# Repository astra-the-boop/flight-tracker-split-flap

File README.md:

# Split flap flight-tracker display
---
## Images

## Whots this UwU?
It's a split flap display with 18 characters designed to show just enough info to track flights. It uses an ESP32 to send API requests to [AviationStack](https://docs.apilayer.com/aviationstack/docs/api-documentation) (oof, only 100 req/mo), and displays the info accordingly.

The display has 3 rows, the first row has 7 characters (1 showing logos, 2 showing airline IATA code, 4 showing flight number), the 2nd row has 6 characters showing the origin and destination airport, the 3rd row has 5 alphanumeric characters and shows flight status (INFLT, DELAY, CNCLD, BRDNG), or time (23:59, 5 DAYS, 5 HRS, 3H49M, etc) which could be configured to different modes (only show status, only show time, or switch between the two).

Each character is its own module and can function independently with 45 character positions each, and the PCB designs makes this simple to do. Each module also includes a magnet and a hall effect sensor for calibration.

## Dimensions
Each module by itself is 9cm wide, up to 14.5cm tall, and up to 10cm thick.
The entire system is 64.3cm wide, 47cm tall, and 15cm thick.

## CAD & PCB
This was designed in Onshape and KiCad.

## Other details:
This uses 1 ESP32 DevKit v1, 2 Arduino Unos, and 1 Arduino Mega. This is not the best way to do it, I only did this because I'm dead broke and that's what i had.
This project uses the MIT License.

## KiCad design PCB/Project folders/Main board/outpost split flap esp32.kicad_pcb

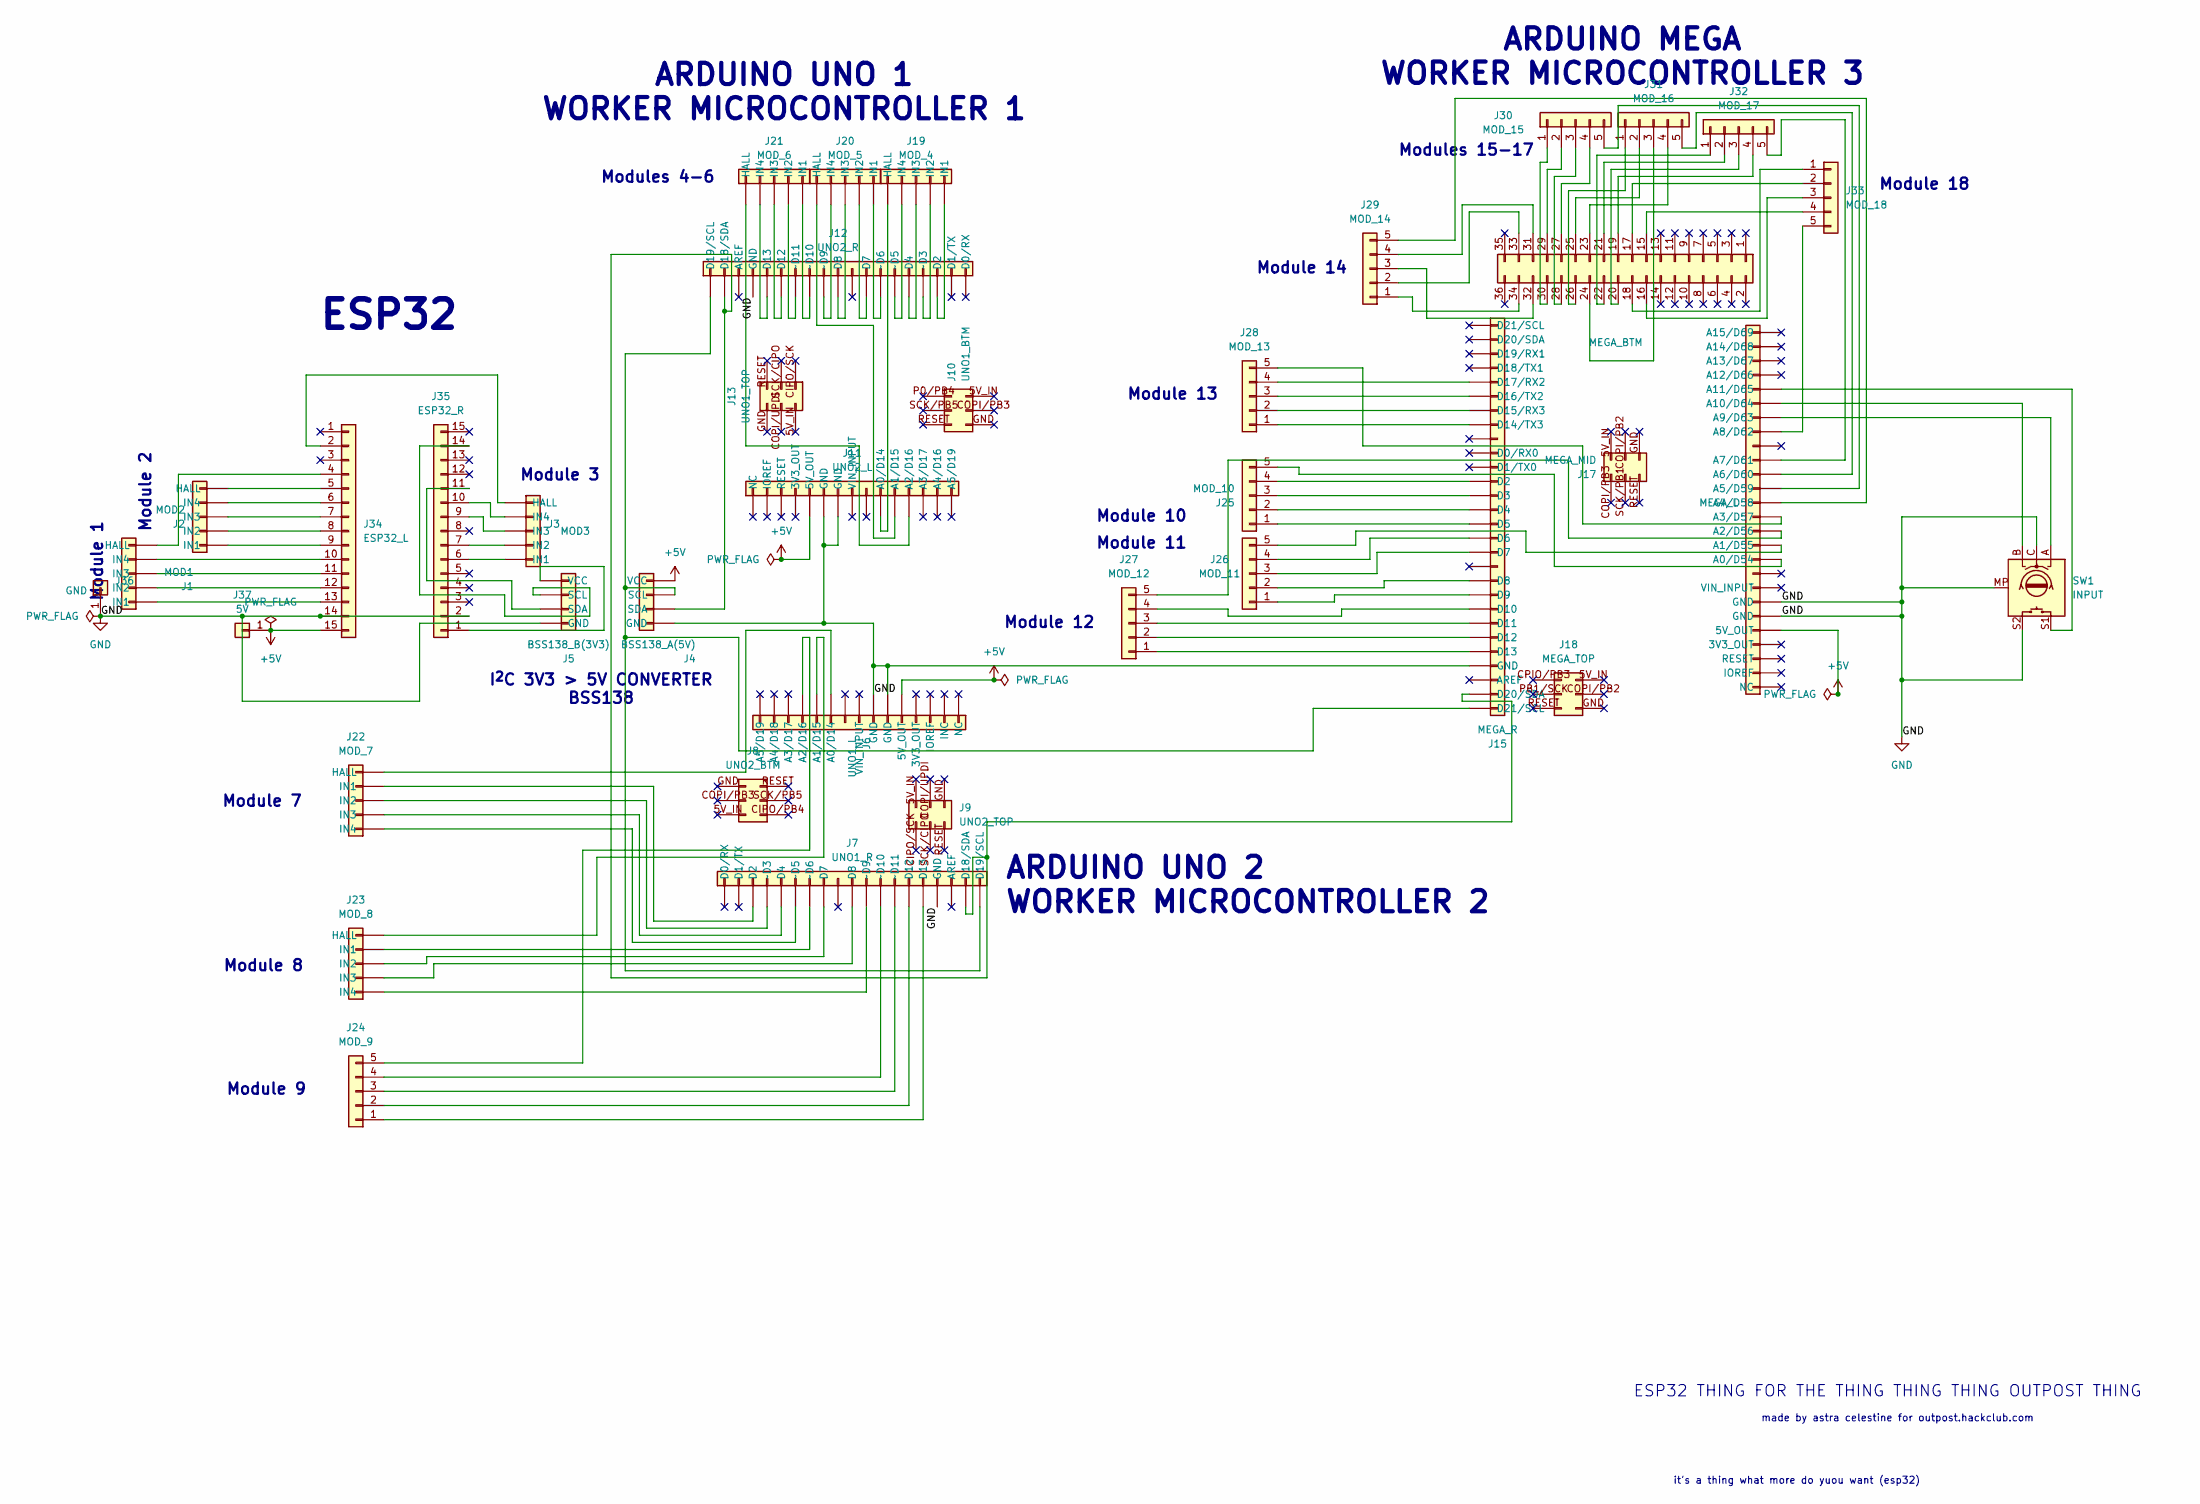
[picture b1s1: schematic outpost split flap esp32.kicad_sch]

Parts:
J1: MOD1; PinHeader_1x05_P2.54mm_Vertical
J2: MOD2; PinHeader_1x05_P2.54mm_Vertical
J3: MOD3; PinHeader_1x05_P2.54mm_Vertical
J4: BSS138_A(5V); PinHeader_1x04_P2.54mm_Vertical
J5: BSS138_B(3V3); PinHeader_1x04_P2.54mm_Vertical
J6: UNO1_L; PinHeader_1x15_P2.54mm_Vertical
J7: UNO1_R; PinHeader_1x19_P2.54mm_Vertical
J8: UNO2_BTM; PinHeader_2x03_P2.54mm_Vertical
J9: UNO2_TOP; PinHeader_2x03_P2.54mm_Vertical
J10: UNO1_BTM; PinHeader_2x03_P2.54mm_Vertical
J11: UNO2_L; PinHeader_1x15_P2.54mm_Vertical
J12: UNO2_R; PinHeader_1x19_P2.54mm_Vertical
J13: UNO1_TOP; PinHeader_2x03_P2.54mm_Vertical
J14: MEGA_L; PinHeader_1x26_P2.54mm_Vertical
J15: MEGA_R; PinHeader_1x28_P2.54mm_Vertical
J16: MEGA_BTM; PinHeader_2x18_P2.54mm_Vertical
J17: MEGA_MID; PinHeader_2x03_P2.54mm_Vertical
J18: MEGA_TOP; PinHeader_2x03_P2.54mm_Vertical
J19: MOD_4; PinHeader_1x05_P2.54mm_Vertical
J20: MOD_5; PinHeader_1x05_P2.54mm_Vertical
J21: MOD_6; PinHeader_1x05_P2.54mm_Vertical
J22: MOD_7; PinHeader_1x05_P2.54mm_Vertical
J23: MOD_8; PinHeader_1x05_P2.54mm_Vertical
J24: MOD_9; PinHeader_1x05_P2.54mm_Vertical
J25: MOD_10; PinHeader_1x05_P2.54mm_Vertical
J26: MOD_11; PinHeader_1x05_P2.54mm_Vertical
J27: MOD_12; PinHeader_1x05_P2.54mm_Vertical
J28: MOD_13; PinHeader_1x05_P2.54mm_Vertical
J29: MOD_14; PinHeader_1x05_P2.54mm_Vertical
J30: MOD_15; PinHeader_1x05_P2.54mm_Vertical
J31: MOD_16; PinHeader_1x05_P2.54mm_Vertical
J32: MOD_17; PinHeader_1x05_P2.54mm_Vertical
J33: MOD_18; PinHeader_1x05_P2.54mm_Vertical
J34: ESP32_L; PinHeader_1x15_P2.54mm_Vertical
J35: ESP32_R; PinHeader_1x15_P2.54mm_Vertical
J36: GND; PinHeader_1x01_P2.54mm_Vertical
J37: 5V; PinHeader_1x01_P2.54mm_Vertical
SW1: INPUT; RotaryEncoder_Alps_EC11E-Switch_Vertical_H20mm

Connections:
+5V: J4.4 (VCC), J6.5 (5V_OUT), J11.5 (5V_OUT), J14.5 (5V_OUT), J34.15, J37.1
GND: J4.1 (GND), J5.4 (GND), J6.6 (GND), J6.7 (GND), J7.16 (GND), J11.6 (GND), J11.7 (GND), J12.4 (GND), J14.6 (GND), J14.7 (GND), J15.25 (GND), J34.14, J35.2, J36.1, SW1.C, SW1.MP, SW1.S2
unnamed: J1.5 (HALL), J34.4
unnamed: J1.1 (IN1), J34.13
unnamed: J1.2 (IN2), J34.12
unnamed: J1.3 (IN3), J34.11
unnamed: J1.4 (IN4), J34.10
unnamed: J2.1 (HALL), J34.5
unnamed: J2.5 (IN1), J34.9
unnamed: J2.4 (IN2), J34.8
unnamed: J2.3 (IN3), J34.7
unnamed: J2.2 (IN4), J34.6
unnamed: J3.5 (HALL), J34.2
unnamed: J3.1 (IN1), J35.6
unnamed: J3.2 (IN2), J35.7
unnamed: J3.3 (IN3), J35.9
unnamed: J3.4 (IN4), J35.10
unnamed: J11.10 (A0/D14), J19.1 (HALL)
unnamed: J11.11 (A1/D15), J20.1 (HALL)
unnamed: J11.12 (A2/D16), J21.1 (HALL)
unnamed: J12.17 (D2), J19.5 (IN1)
unnamed: J12.15 (D4), J19.3 (IN3)
unnamed: J12.12 (D7), J20.4 (IN2)
unnamed: J12.10 (D8), J20.3 (IN3)
unnamed: J12.6 (D12), J21.3 (IN3)
unnamed: J12.5 (D13), J21.2 (IN4)
unnamed: J4.2 (SDA), J7.18 (D18/SDA), J12.2 (D18/SDA), J15.27 (D20/SDA)
unnamed: J4.3 (SCL), J7.19 (D19/SCL), J12.1 (D19/SCL), J15.28 (D21/SCL)
unnamed: J12.16 (~D3), J19.4 (IN2)
unnamed: J12.14 (~D5), J19.2 (IN4)
unnamed: J12.13 (~D6), J20.5 (IN1)
unnamed: J12.9 (~D9), J20.2 (IN4)
unnamed: J12.8 (~D10), J21.5 (IN1)
unnamed: J12.7 (~D11), J21.4 (IN2)
unnamed: J14.10 (A0/D54), J25.5 (HALL)
unnamed: J14.11 (A1/D55), J26.5 (HALL)
unnamed: J14.12 (A2/D56), J27.5 (HALL)
unnamed: J14.13 (A3/D57), J28.5 (HALL)
unnamed: J14.14 (A4/D58), J29.5 (HALL)
unnamed: J14.15 (A5/D59), J30.5 (HALL)
unnamed: J14.16 (A6/D60), J31.5 (HALL)
unnamed: J14.17 (A7/D61), J32.5 (HALL)
unnamed: J14.19 (A8/D62), J33.5 (HALL)
unnamed: J14.20 (A9/D63), SW1.A
unnamed: J14.21 (A10/D64), SW1.B
unnamed: J14.22 (A11/D65), SW1.S1
unnamed: J15.12 (D2), J25.4 (IN1)
unnamed: J15.13 (D3), J25.3 (IN2)
unnamed: J15.14 (D4), J25.2 (IN3)
unnamed: J15.15 (D5), J25.1 (IN4)
unnamed: J15.16 (D6), J26.4 (IN1)
unnamed: J15.17 (D7), J26.3 (IN2)
unnamed: J15.19 (D8), J26.2 (IN3)
unnamed: J15.20 (D9), J26.1 (IN4)
unnamed: J15.21 (D10), J27.4 (IN1)
unnamed: J15.22 (D11), J27.3 (IN2)
unnamed: J15.23 (D12), J27.2 (IN3)
unnamed: J15.24 (D13), J27.1 (IN4)
unnamed: J15.8 (D14/TX3), J28.1 (IN1)
unnamed: J15.7 (D15/RX3), J28.2 (IN2)
unnamed: J15.6 (D16/TX2), J28.3 (IN3)
unnamed: J15.5 (D17/RX2), J28.4 (IN4)
unnamed: J16.34 (D22), J29.1 (IN1)
unnamed: J16.33 (D23), J29.2 (IN2)
unnamed: J16.32 (D24), J29.3 (IN3)
unnamed: J16.31 (D25), J29.4 (IN4)
unnamed: J16.30 (D26), J30.1 (IN1)
unnamed: J16.29 (D27), J30.2 (IN2)
unnamed: J16.28 (D28), J30.3 (IN3)
unnamed: J16.27 (D29), J30.4 (IN4)
unnamed: J16.26 (D30), J31.1 (IN1)
unnamed: J16.25 (D31), J31.2 (IN2)
unnamed: J16.24 (D32), J31.3 (IN3)
unnamed: J16.23 (D33), J31.4 (IN4)
unnamed: J16.22 (D34), J32.1 (IN1)
unnamed: J16.21 (D35), J32.2 (IN2)
unnamed: J16.20 (D36), J32.3 (IN3)
unnamed: J16.19 (D37), J32.4 (IN4)
unnamed: J16.18 (D38), J33.1 (IN1)
unnamed: J16.17 (D39), J33.2 (IN2)
unnamed: J16.16 (D40), J33.3 (IN3)
unnamed: J16.15 (D41), J33.4 (IN4)
unnamed: J6.10 (A0/D14), J22.5 (HALL)
unnamed: J7.3 (D2), J22.4 (IN1)
unnamed: J7.4 (~D3), J22.3 (IN2)
unnamed: J7.5 (D4), J22.2 (IN3)
unnamed: J7.6 (~D5), J22.1 (IN4)
unnamed: J6.11 (A1/D15), J23.5 (HALL)
unnamed: J7.7 (~D6), J23.4 (IN1)
unnamed: J7.8 (D7), J23.3 (IN2)
unnamed: J7.10 (D8), J23.2 (IN3)
unnamed: J7.11 (~D9), J23.1 (IN4)
unnamed: J6.12 (A2/D16), J24.5 (HALL)
unnamed: J7.12 (~D10), J24.4 (IN1)
unnamed: J7.13 (~D11), J24.3 (IN2)
unnamed: J7.14 (D12), J24.2 (IN3)
unnamed: J7.15 (D13), J24.1 (IN4)
unnamed: J5.1 (VCC), J35.1
unnamed: J5.3 (SDA), J35.11
unnamed: J5.2 (SCL), J35.14

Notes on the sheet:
Modules 4-6
Module 13
Module 3
Module 18
it's a thing what more do yuou want (esp32)
Module 10
ESP32 THING FOR THE THING THING THING OUTPOST THING
I^{2}C 3V3 > 5V CONVERTER BSS138
Modules 15-17
Module 11
ARDUINO MEGA WORKER MICROCONTROLLER 3
Module 8
Module 7
Module 1
Module 12
ESP32
ARDUINO UNO 2 WORKER MICROCONTROLLER 2
Module 14
made by astra celestine for outpost.hackclub.com
ARDUINO UNO 1 WORKER MICROCONTROLLER 1
Module 9
Module 2

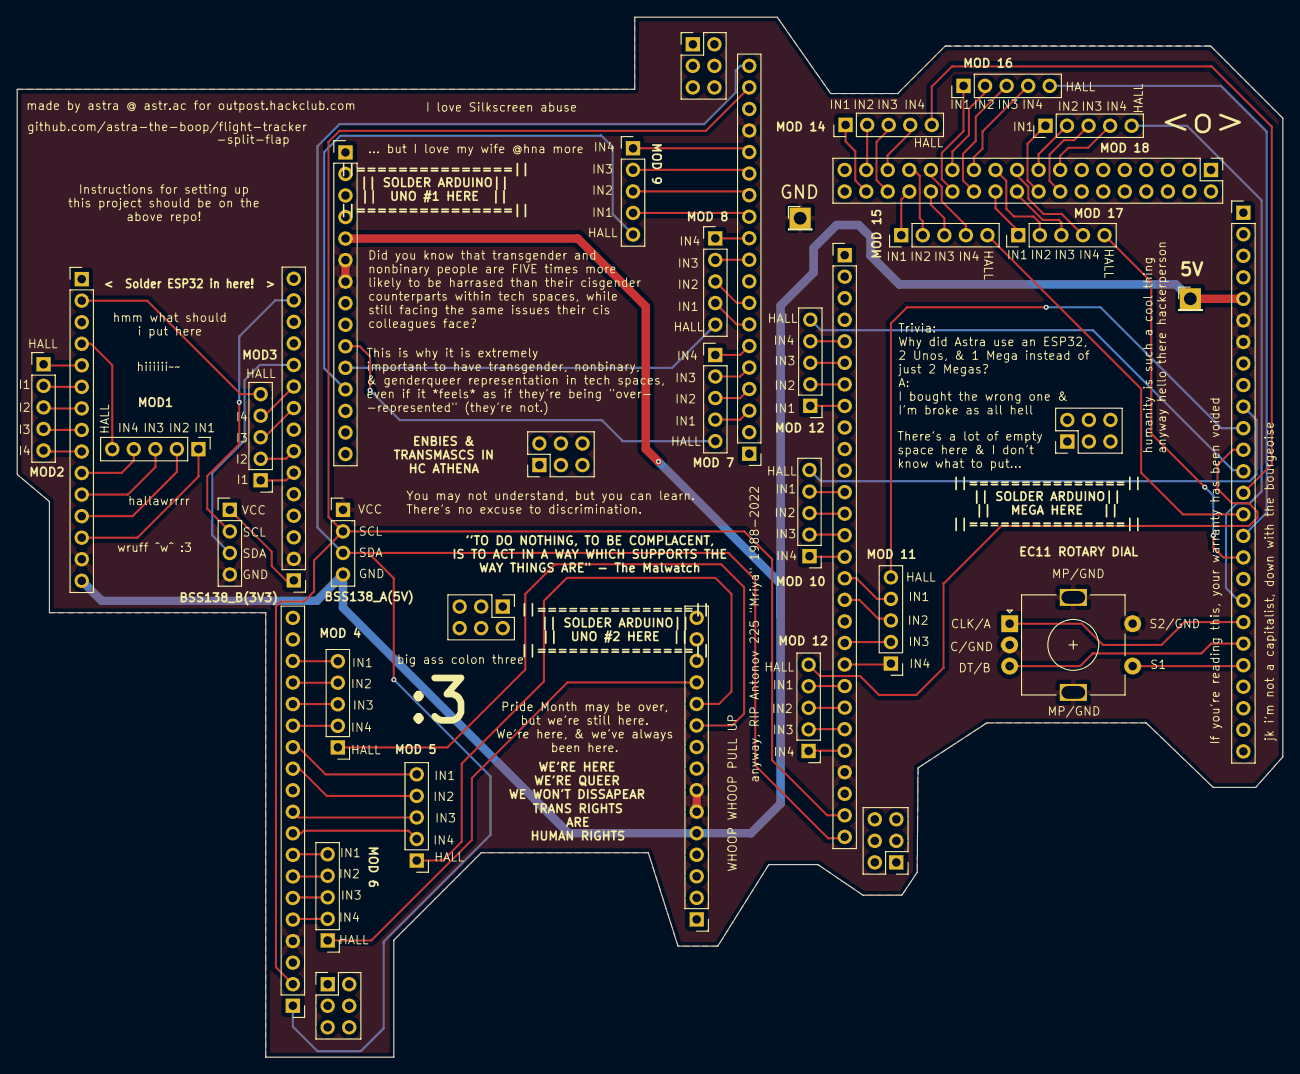
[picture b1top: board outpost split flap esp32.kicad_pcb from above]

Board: 2 copper layers, 149.2 x 122.6 mm, 38 parts (0 on the bottom side), 100 nets.

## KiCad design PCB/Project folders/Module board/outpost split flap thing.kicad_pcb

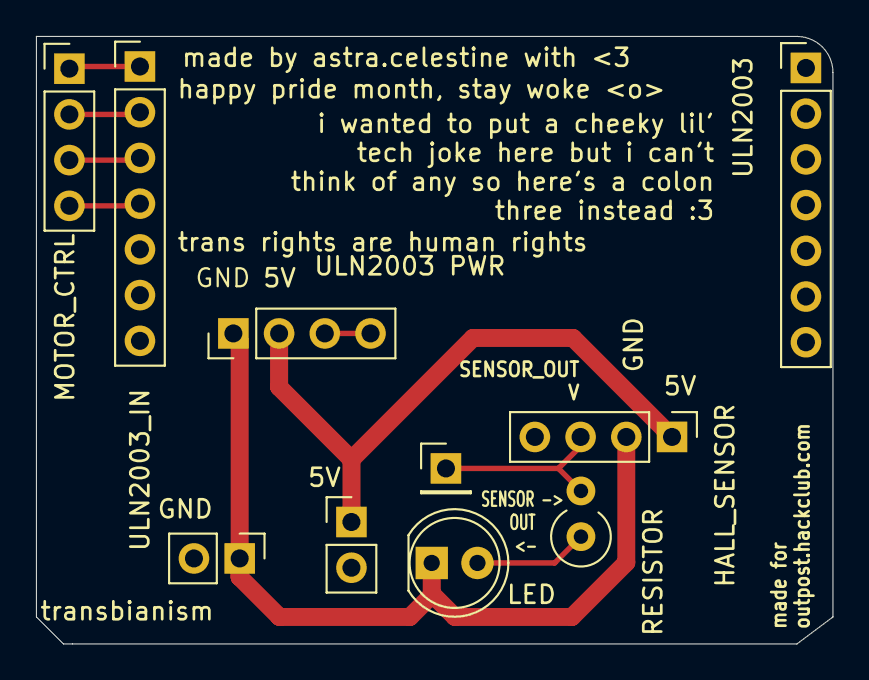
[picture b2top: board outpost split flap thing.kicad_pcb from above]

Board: 2 copper layers, 44.2 x 33.8 mm, 10 parts (0 on the bottom side), 9 nets.

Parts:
D1: LED; LED_D5.0mm
J1: MOTOR_CTRL; PinHeader_1x04_P2.54mm_Vertical
J2: SENSOR_OUT; PinHeader_1x01_P2.54mm_Vertical
J3: HALL_SENSOR; PinHeader_1x04_P2.54mm_Vertical
J4: 5V; PinHeader_1x02_P2.54mm_Vertical
J5: ULN2003_IN; PinHeader_1x07_P2.54mm_Vertical
J6: ULN2003 PWR; PinHeader_1x04_P2.54mm_Vertical
J7: ULN2003; PinHeader_1x07_P2.54mm_Vertical
J8: GND; PinHeader_1x02_P2.54mm_Vertical
R1: RESISTOR; R_Axial_DIN0309_L9.0mm_D3.2mm_P2.54mm_Vertical

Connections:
+5V: J3.1, J4.1, J6.2
/IN1: J1.1, J5.1
/IN2: J1.2, J5.2
/IN3: J1.3, J5.3
/IN4: J1.4, J5.4
/SENSOR_OUT: J2.1, J3.3, R1.2
GND: D1.1 (K), J3.2, J6.1, J8.1
unnamed: D1.2 (A), R1.1
unnamed: J6.3, J6.4
